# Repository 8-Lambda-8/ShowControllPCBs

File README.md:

A collection of PCBs with faders, buttons, encoders (and so on ...) for usage in an MIDI or OSC controller

Interactive BOMs:

[Fader PCB](https://htmlpreview.github.io/?https://raw.githubusercontent.com/8-Lambda-8/ShowControllPCBs/main/faderBoard/bom/ibom.html)

[Button Matrix PCB](https://htmlpreview.github.io/?https://raw.githubusercontent.com/8-Lambda-8/ShowControllPCBs/main/buttonMatrixBoard/bom/ibom.html)

[CAT-XLR Adapter PCB](https://htmlpreview.github.io/?https://raw.githubusercontent.com/8-Lambda-8/ShowControllPCBs/main/CAT_XLR/bom/ibom.html)

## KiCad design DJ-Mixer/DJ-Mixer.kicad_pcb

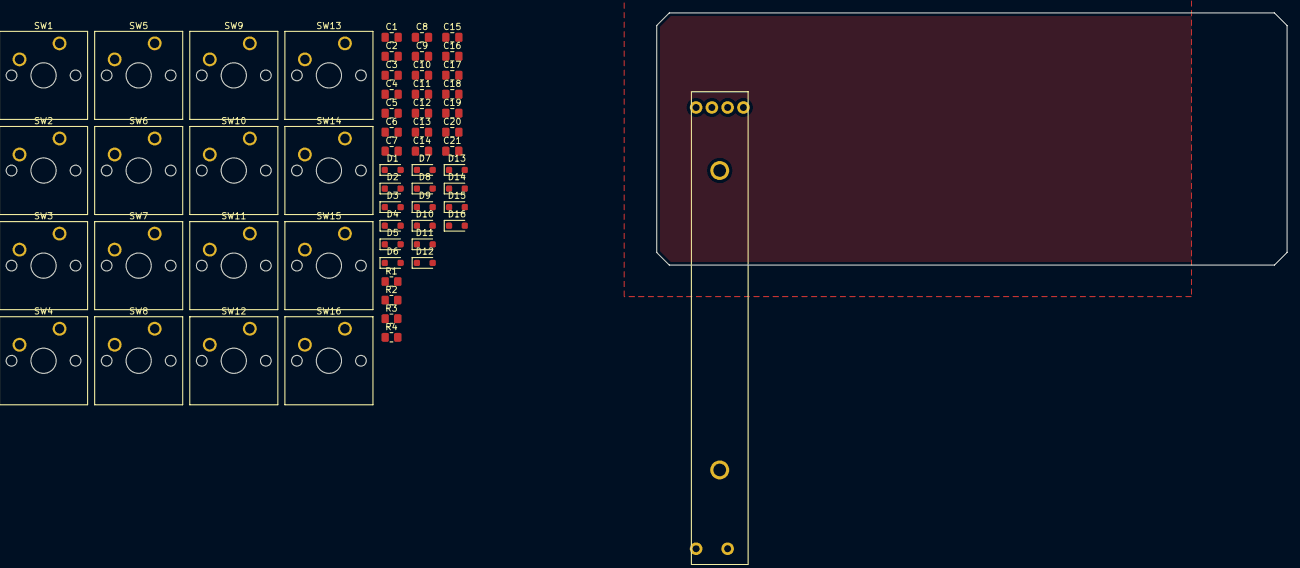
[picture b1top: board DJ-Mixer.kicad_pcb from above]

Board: 2 copper layers, 100.0 x 40.0 mm, 58 parts (0 on the bottom side), 24 nets, no tracks yet.

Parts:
C1, C2, C3, C4, C5, C6, C7, C8, C9, C10, C11, C12, C13, C14, C15, C16, C17, C18, C19, C20, C21: 100nF; C_0805_2012Metric_Pad1.18x1.45mm_HandSolder
D1, D2, D3, D4, D5, D6, D7, D8, D9, D10, D11, D12, D13, D14, D15, D16: 1N4148WS; D_SOD-323_HandSoldering
R1, R2, R3, R4: 10k; R_0805_2012Metric_Pad1.20x1.40mm_HandSolder
RV4: Fader_B10k; Fader B10K
SW1, SW2, SW3, SW4, SW5, SW6, SW7, SW8, SW9, SW10, SW11, SW12, SW13, SW14, SW15, SW16: SW_Push; SW_Cherry_MX_1.00u_PCB

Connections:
Fader4: C4.2, C5.2
GND: C1.1, C2.1, C3.1, C4.1, C5.1, C6.1, C7.1, C8.1, C9.1, C10.1, C11.1, C12.1, C13.1, C14.1, C15.1, C16.1, C17.1, C18.1, C19.1, C20.1, C21.1
unnamed: D1.2 (A), SW1.2
unnamed: D2.2 (A), SW2.2
unnamed: D3.2 (A), SW3.2
unnamed: D4.2 (A), SW4.2
unnamed: D5.2 (A), SW5.2
unnamed: D6.2 (A), SW6.2
unnamed: D7.2 (A), SW7.2
unnamed: D8.2 (A), SW8.2
unnamed: D9.2 (A), SW9.2
unnamed: D10.2 (A), SW10.2
unnamed: D11.2 (A), SW11.2
unnamed: D12.2 (A), SW12.2
unnamed: D13.2 (A), SW13.2
unnamed: D14.2 (A), SW14.2
unnamed: D15.2 (A), SW15.2
unnamed: D16.2 (A), SW16.2
Pull1: D1.1 (K), D2.1 (K), D3.1 (K), D4.1 (K)
Pull2: D5.1 (K), D6.1 (K), D7.1 (K), D8.1 (K)
Pull3: D9.1 (K), D10.1 (K), D11.1 (K), D12.1 (K), R1.2, R2.2, R3.2, SW1.1, SW2.1, SW3.1, SW5.1, SW6.1, SW7.1, SW9.1, SW10.1, SW11.1, SW13.1, SW14.1, SW15.1
Pull4: D13.1 (K), D14.1 (K), D15.1 (K), D16.1 (K)
Sense4: R4.2, SW4.1, SW8.1, SW12.1, SW16.1
VCC: C6.2, C7.2, C8.2, C9.2, C10.2, C11.2, C12.2, C13.2, C14.2, C15.2, C16.2, C17.2, C18.2, C19.2, C20.2, C21.2, R1.1, R2.1, R3.1, R4.1

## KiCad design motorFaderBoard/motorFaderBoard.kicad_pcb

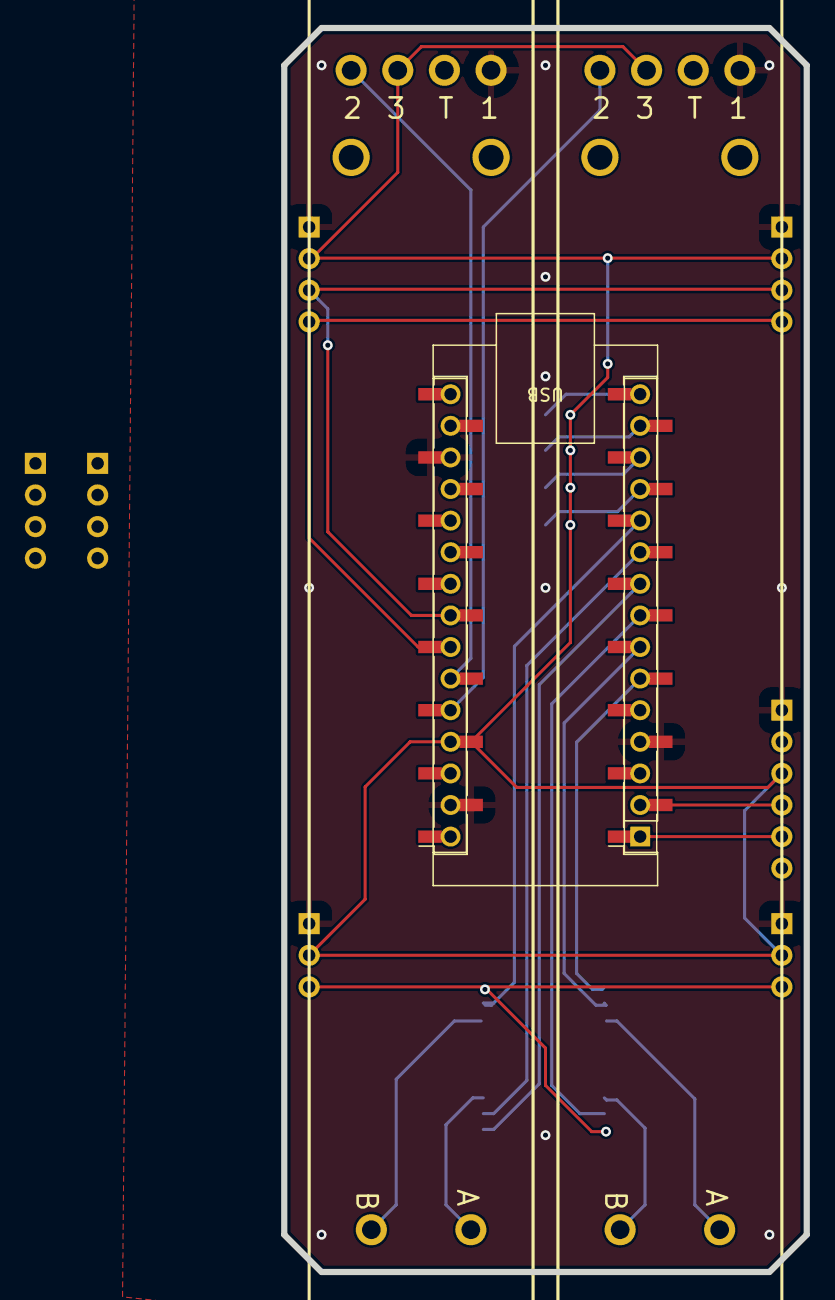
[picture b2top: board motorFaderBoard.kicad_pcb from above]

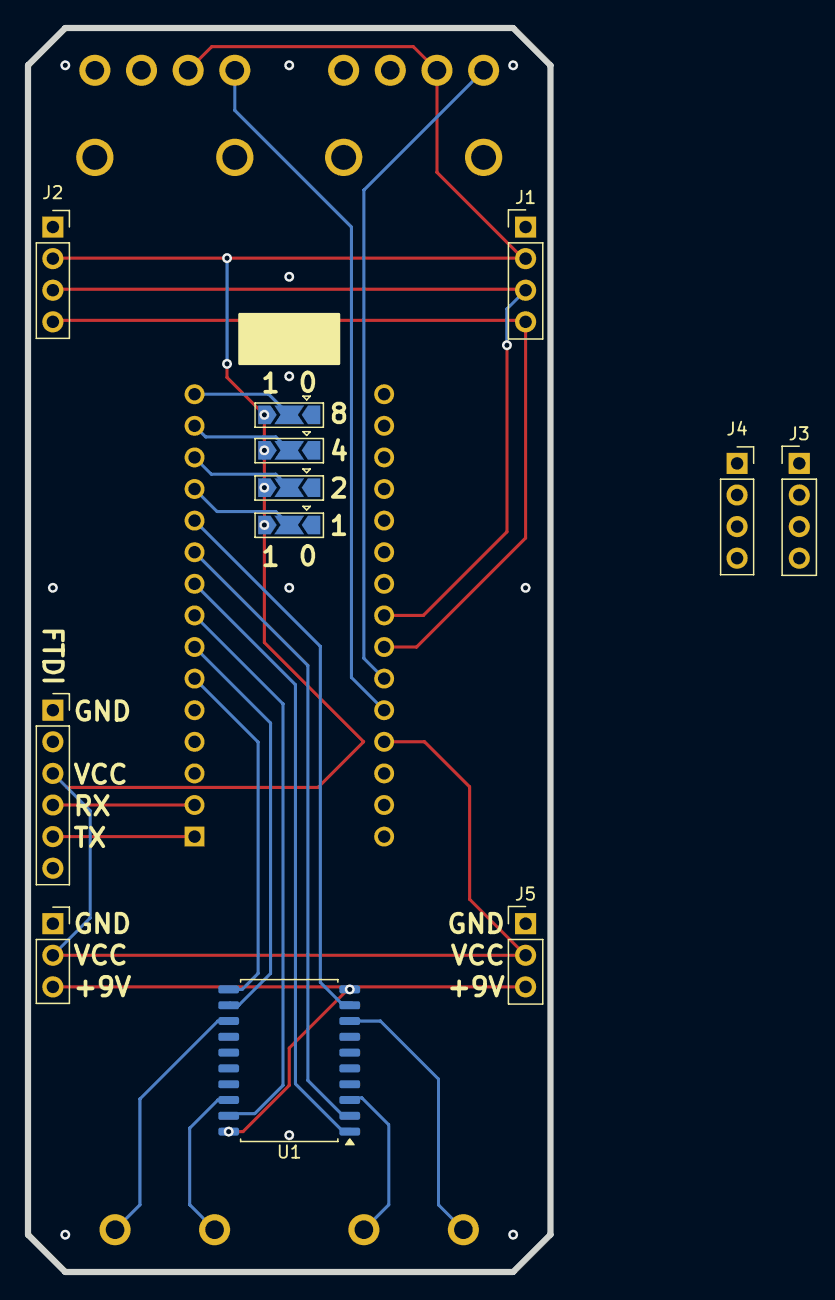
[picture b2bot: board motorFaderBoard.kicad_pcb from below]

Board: 2 copper layers, 42.0 x 100.0 mm, 17 parts (12 on the bottom side), 33 nets.

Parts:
A1: Arduino_Nano_v3.x; Arduino_Nano
J1, J3: Conn_01x04_Pin; PinHeader_1x04_P2.54mm_Vertical
J2, J4: Conn_01x04_Socket; PinSocket_1x04_P2.54mm_Vertical
J5: Conn_01x03_Pin; PinHeader_1x03_P2.54mm_Vertical
J6: Conn_01x03_Socket; PinSocket_1x03_P2.54mm_Vertical
J7, J8: Conn_01x15_Socket; PinSocket_1x15_P2.54mm_Vertical_SMD_Pin1Right
J9: Conn_01x06_Socket; PinSocket_1x06_P2.54mm_Vertical
JP1, JP2, JP3, JP4: SolderJumper_3_Open; SolderJumper-3_P2.0mm_Open_TrianglePad1.0x1.5mm
RV1, RV2: RES-TH_L146.5-W18.0_RSA0N11M9A07
U1: L293DD; Infineon_SOIC-20W_7.6x12.8mm_P1.27mm

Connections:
+9V: J5.3, J6.3, U1.10 (VS), U1.20 (VSS)
ADDR_1: A1.12 (D9), J7.12, JP1.2 (C)
ADDR_2: A1.13 (D10), J7.13, JP2.2 (C)
ADDR_4: A1.14 (D11), J7.14, JP3.2 (C)
ADDR_8: A1.15 (D12), J7.15, JP4.2 (C)
Fader1: A1.25 (A6), J8.6, RV1.2
Fader2: A1.26 (A7), J8.5, RV2.2
GND: A1.4 (GND), A1.18 (AREF), A1.29 (GND), J1.1, J2.1, J3.1, J4.1, J5.1, J6.1, J7.4, J8.2, J8.13, J9.1, JP1.1 (A), JP2.1 (A), JP3.1 (A), JP4.1 (A), RV1.1, RV2.1, U1.4 (GND), U1.5 (GND), U1.6 (GND), U1.7 (GND), U1.14 (GND), U1.15 (GND), U1.16 (GND), U1.17 (GND)
M1A: RV1.A, U1.3 (OUTPUT_1)
M1A_I: A1.10 (D7), J7.10, U1.2 (INPUT_1)
M1B: RV1.B, U1.8 (OUTPUT_2)
M1B_I: A1.11 (D8), J7.11, U1.9 (INPUT_2)
M1E: A1.9 (D6), J7.9, U1.1 (ENABLE_1)
M2A: RV2.A, U1.13 (OUTPUT_3)
M2A_I: A1.7 (D4), J7.7, U1.12 (INPUT_3)
M2B: RV2.B, U1.18 (OUTPUT_4)
M2B_I: A1.8 (D5), J7.8, U1.19 (INPUT_4)
M2E: A1.6 (D3), J7.6, U1.11 (ENABLE_2)
RX: A1.2 (D0/RX), J7.2, J9.4
SCL: A1.24 (A5), J1.4, J2.4, J3.4, J4.4, J8.7
SDA: A1.23 (A4), J1.3, J2.3, J3.3, J4.3, J8.8
TX: A1.1 (D1/TX), J7.1, J9.5
VCC: A1.27 (+5V), J1.2, J2.2, J3.2, J4.2, J5.2, J6.2, J8.4, J9.3, JP1.3 (B), JP2.3 (B), JP3.3 (B), JP4.3 (B), RV1.3, RV2.3
X3V3: A1.17 (3V3), J8.14
XA0: A1.19 (A0), J8.12
XA1: A1.20 (A1), J8.11
XA2: A1.21 (A2), J8.10
XA3: A1.22 (A3), J8.9
XD2: A1.5 (D2), J7.5
XD13: A1.16 (D13), J8.15
XRST: A1.3 (~RESET), J7.3
XRST2: A1.28 (~RESET), J8.3
XVIN: A1.30 (VIN), J8.1

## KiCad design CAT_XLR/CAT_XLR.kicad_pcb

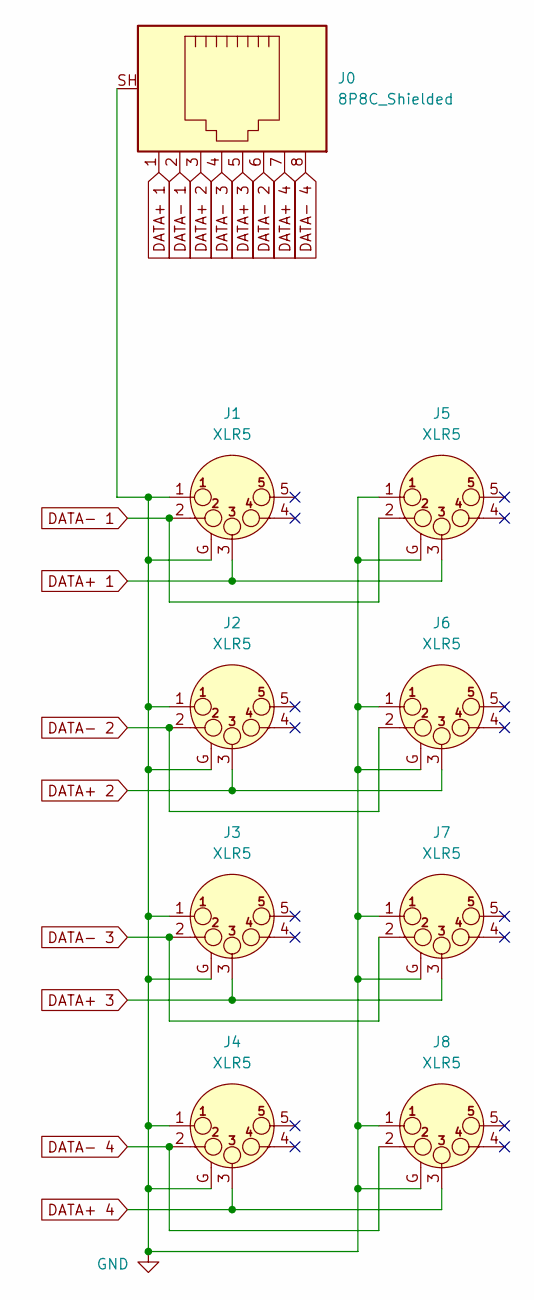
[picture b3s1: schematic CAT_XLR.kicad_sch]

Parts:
J0: 8P8C_Shielded; RJ45_Ninigi_GE
J1, J2, J3, J4: XLR5; Jack_XLR_Neutrik_NC3+5FAH2-0_Horizontal
J5, J6, J7, J8: XLR5; Jack_XLR_Neutrik_NC3+5MAH_Horizontal

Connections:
DATA+ 1: J0.1, J1.3, J5.3
DATA+ 2: J0.3, J2.3, J6.3
DATA+ 3: J0.5, J3.3, J7.3
DATA+ 4: J0.7, J4.3, J8.3
DATA- 1: J0.2, J1.2, J5.2
DATA- 2: J0.6, J2.2, J6.2
DATA- 3: J0.4, J3.2, J7.2
DATA- 4: J0.8, J4.2, J8.2
GND: J0.SH, J1.1, J1.G, J2.1, J2.G, J3.1, J3.G, J4.1, J4.G, J5.1, J5.G, J6.1, J6.G, J7.1, J7.G, J8.1, J8.G

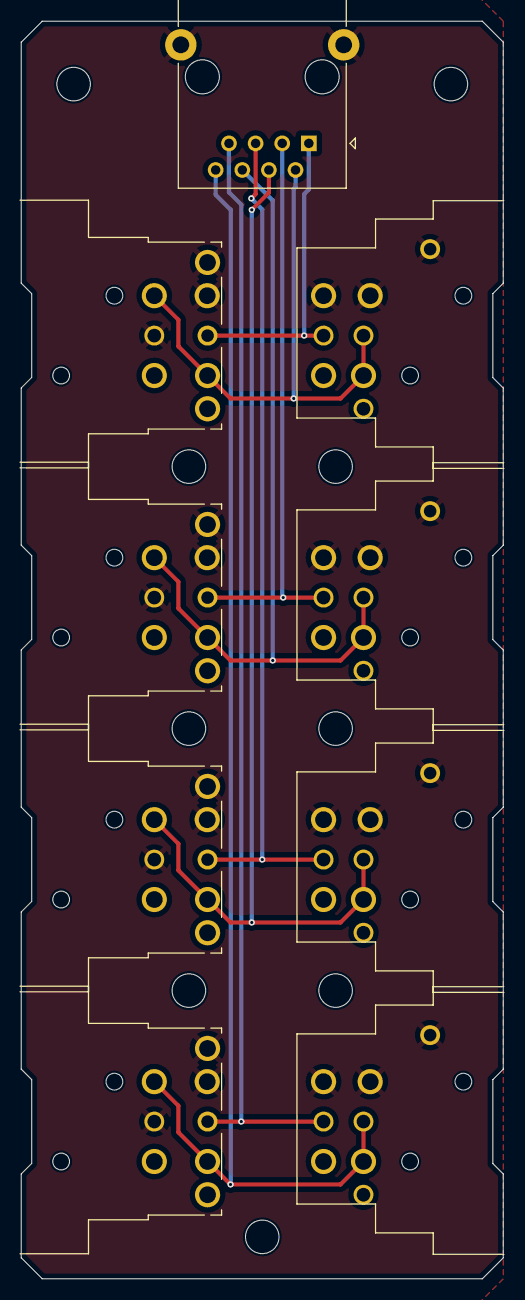
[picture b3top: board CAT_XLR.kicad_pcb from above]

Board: 2 copper layers, 46.0 x 120.0 mm, 9 parts (0 on the bottom side), 9 nets.

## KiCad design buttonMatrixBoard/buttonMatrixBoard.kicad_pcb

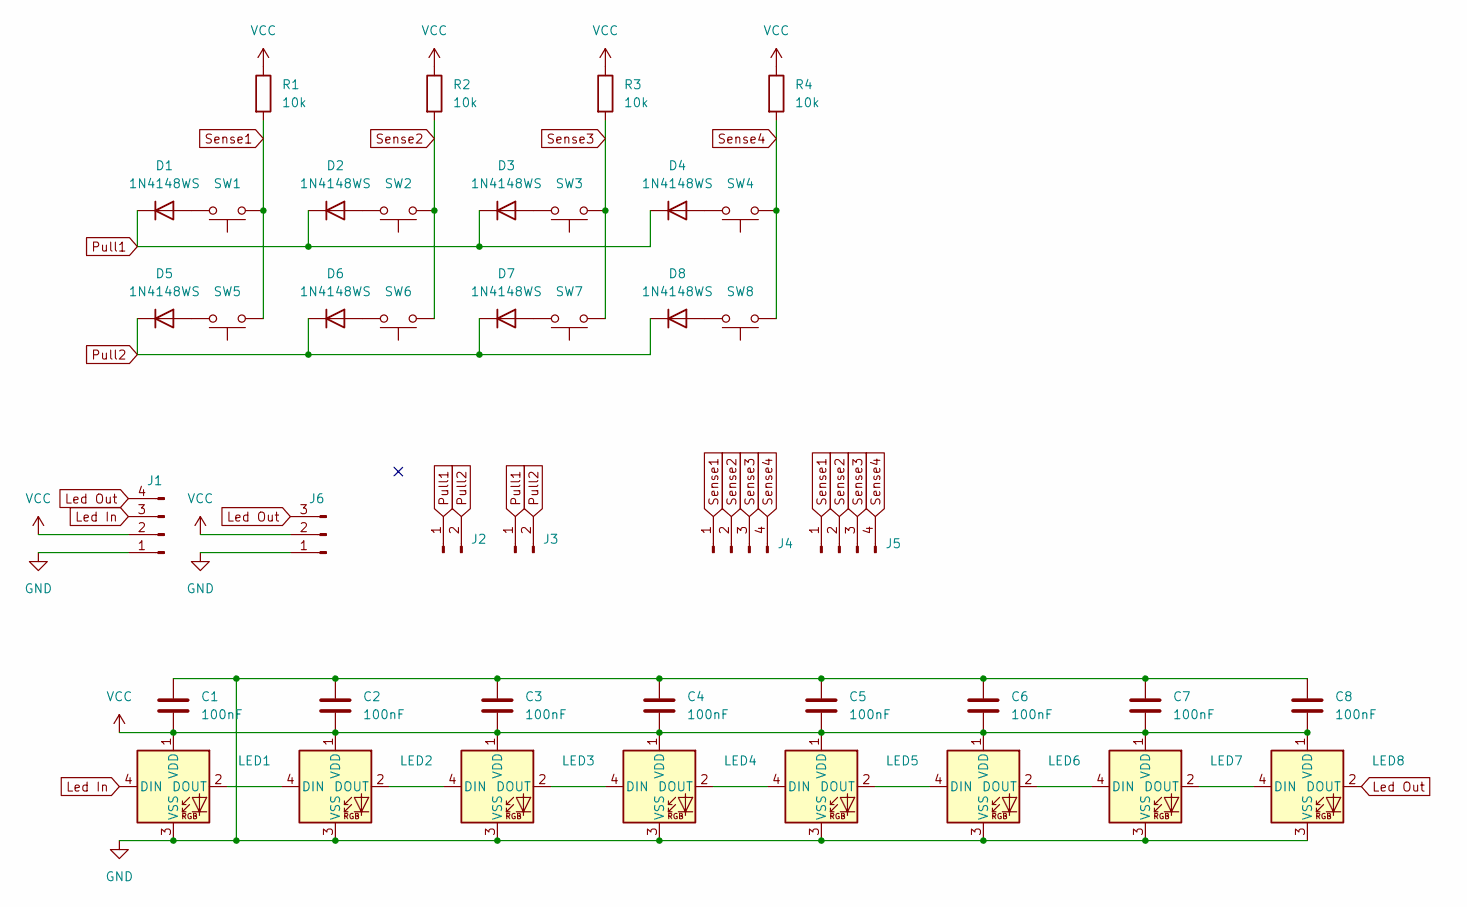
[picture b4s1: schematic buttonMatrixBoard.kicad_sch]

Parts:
C1, C2, C3, C4, C5, C6, C7, C8: 100nF; C_0805_2012Metric_Pad1.18x1.45mm_HandSolder
D1, D2, D3, D4, D5, D6, D7, D8: 1N4148WS; D_SOD-323_HandSoldering
J1, J4, J5: Conn_01x04_Pin; PinHeader_1x04_P2.54mm_Vertical
J2, J3: Conn_01x02_Pin; PinHeader_1x02_P2.54mm_Vertical
J6: Conn_01x03_Pin; PinHeader_1x03_P2.54mm_Vertical
LED1, LED2, LED3, LED4, LED5, LED6, LED7, LED8: WS2812B; WS2812_embedded
R1, R2, R3, R4: 10k; R_0805_2012Metric_Pad1.20x1.40mm_HandSolder
SW1, SW2, SW3, SW4, SW5, SW6, SW7, SW8: SW_Push; SW_Cherry_MX_1.00u_PCB

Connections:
GND: C1.1, C2.1, C3.1, C4.1, C5.1, C6.1, C7.1, C8.1, J1.1, J6.1, LED1.3 (VSS), LED2.3 (VSS), LED3.3 (VSS), LED4.3 (VSS), LED5.3 (VSS), LED6.3 (VSS), LED7.3 (VSS), LED8.3 (VSS)
Led In: J1.3, LED1.4 (DIN)
Led Out: J1.4, J6.3, LED8.2 (DOUT)
unnamed: D1.2 (A), SW1.2
unnamed: D2.2 (A), SW2.2
unnamed: D3.2 (A), SW3.2
unnamed: D4.2 (A), SW4.2
unnamed: D5.2 (A), SW5.2
unnamed: D6.2 (A), SW6.2
unnamed: D7.2 (A), SW7.2
unnamed: D8.2 (A), SW8.2
unnamed: LED1.2 (DOUT), LED2.4 (DIN)
unnamed: LED2.2 (DOUT), LED3.4 (DIN)
unnamed: LED3.2 (DOUT), LED4.4 (DIN)
unnamed: LED4.2 (DOUT), LED5.4 (DIN)
unnamed: LED5.2 (DOUT), LED6.4 (DIN)
unnamed: LED6.2 (DOUT), LED7.4 (DIN)
unnamed: LED7.2 (DOUT), LED8.4 (DIN)
Pull1: D1.1 (K), D2.1 (K), D3.1 (K), D4.1 (K), J2.1, J3.1
Pull2: D5.1 (K), D6.1 (K), D7.1 (K), D8.1 (K), J2.2, J3.2
Sense1: J4.1, J5.1, R1.2, SW1.1, SW5.1
Sense2: J4.2, J5.2, R2.2, SW2.1, SW6.1
Sense3: J4.3, J5.3, R3.2, SW3.1, SW7.1
Sense4: J4.4, J5.4, R4.2, SW4.1, SW8.1
VCC: C1.2, C2.2, C3.2, C4.2, C5.2, C6.2, C7.2, C8.2, J1.2, J6.2, LED1.1 (VDD), LED2.1 (VDD), LED3.1 (VDD), LED4.1 (VDD), LED5.1 (VDD), LED6.1 (VDD), LED7.1 (VDD), LED8.1 (VDD), R1.1, R2.1, R3.1, R4.1

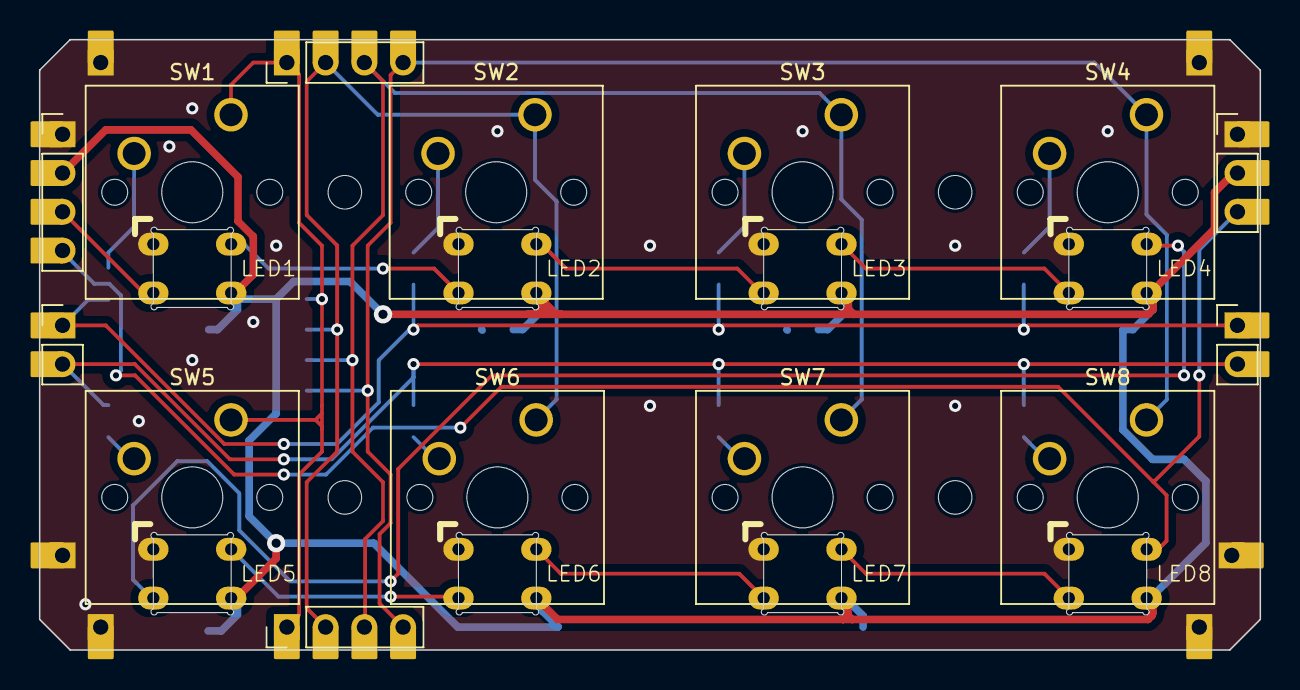
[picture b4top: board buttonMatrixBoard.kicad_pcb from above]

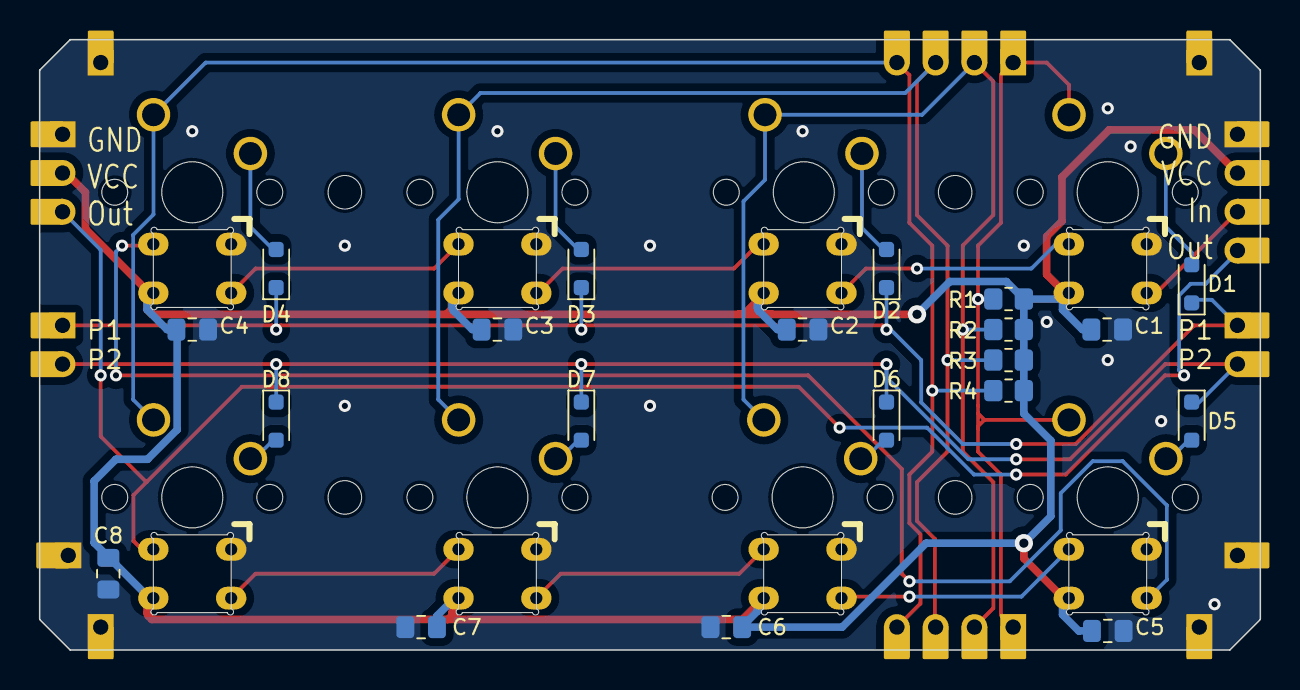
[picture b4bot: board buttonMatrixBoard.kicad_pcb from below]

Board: 2 copper layers, 80.0 x 40.0 mm, 42 parts (20 on the bottom side), 25 nets.
